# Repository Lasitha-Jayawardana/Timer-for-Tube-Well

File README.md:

# Timer-for-Tube-Well
Automated water filling system with dual motor including Tube well and upper tank.

# Tips
This include Arduino file and Eagle cad PCB project. And also Camout and CNC milling files are in here with.

First tank fill from the tube well using On and Off timer for tube well motor.
Second Tank fill from first tank by different motor.
Water level is measured by Sona Sensor in each tank. 
After full filled each tank, each motors are temporaly wait till water level goes down.

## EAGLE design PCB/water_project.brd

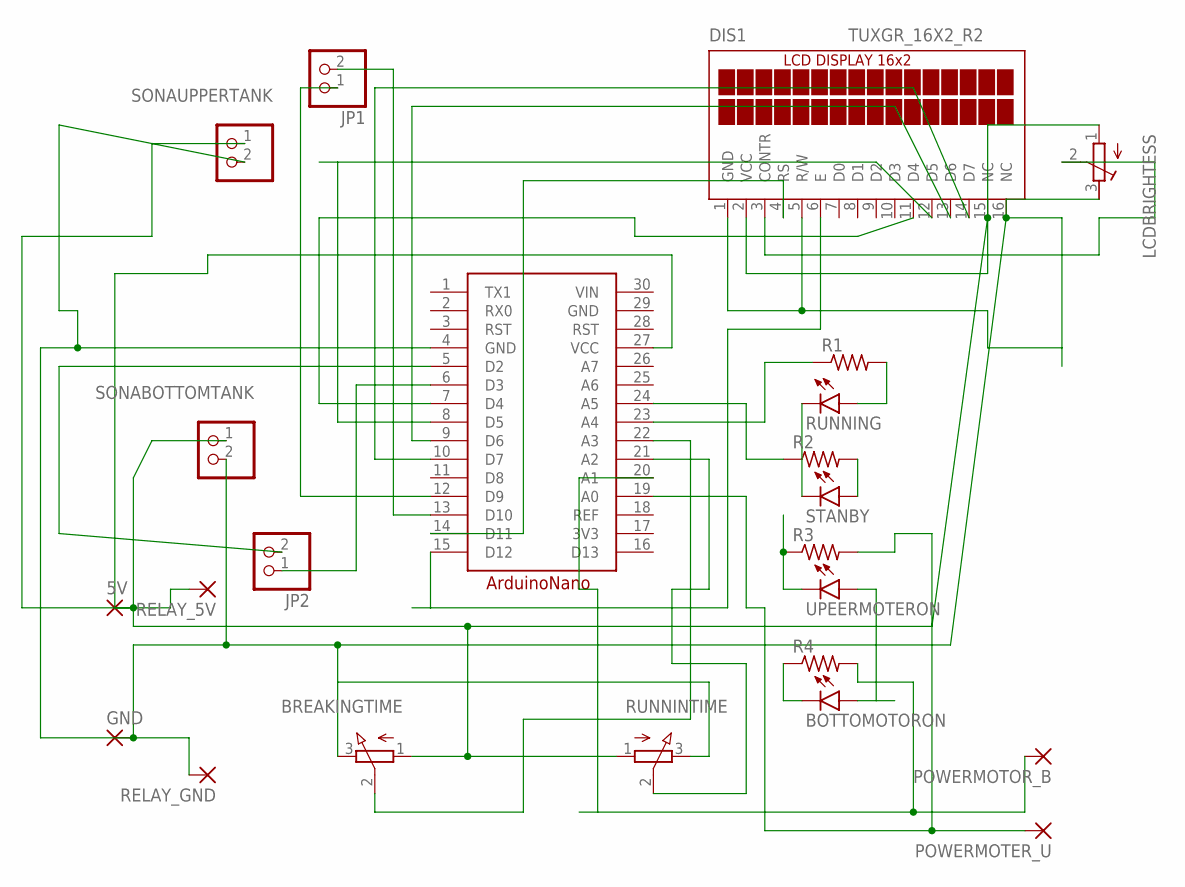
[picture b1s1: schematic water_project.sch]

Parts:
5V: 3,17/1,3
A1: ARDUINONANO
BOTTOMOTORON: LEDSFH480; SFH480
BREAKINGTIME: 3RP/1610N
DIS1: TUXGR_16X2_R2
GND: 3,17/1,3
JP1, JP2: PINHD-1X2; 1X02
LCDBRIGHTESS: R-TRIMM3339P; RTRIM3339P
POWERMOTER_U: 3,17/1,3
POWERMOTOR_B: 3,17/1,3
R1, R2, R3, R4: R-US_0207/7; 0207/7
RELAY_5V: 3,17/1,3
RELAY_GND: 3,17/1,3
RUNNING: LEDSFH480; SFH480
RUNNINTIME: 3RP/1610N
SONABOTTOMTANK: PINHD-1X2; 1X02
SONAUPPERTANK: PINHD-1X2; 1X02
STANBY: LEDSFH480; SFH480
UPEERMOTERON: LEDSFH480; SFH480

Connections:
3V3: A1.17 (3V3)
ECHO: A1.13 (D10), JP1.2
ECHO1: A1.5 (D2), JP2.2
GND: A1.4 (GND), A1.29 (GND), BREAKINGTIME.3 (E), DIS1.1 (GND), DIS1.5 (R/W), DIS1.16 (NC), GND.1, LCDBRIGHTESS.3 (E), RELAY_GND.1, RUNNINTIME.3 (E), SONABOTTOMTANK.2, SONAUPPERTANK.2
unnamed: R1.2, RUNNING.A
unnamed: R2.2, STANBY.A
unnamed: BOTTOMOTORON.K (C), R4.1
unnamed: DIS1.3 (CONTR), LCDBRIGHTESS.2 (S)
unnamed: A1.7 (D4), DIS1.11 (D4)
unnamed: A1.8 (D5), DIS1.12 (D5)
unnamed: A1.9 (D6), DIS1.13 (D6)
unnamed: A1.10 (D7), DIS1.14 (D7)
unnamed: RUNNING.K (C), STANBY.K (C)
unnamed: A1.14 (D11), DIS1.4 (RS)
unnamed: A1.15 (D12), DIS1.6 (E)
unnamed: A1.21 (A2), RUNNINTIME.2 (S)
unnamed: A1.22 (A3), BREAKINGTIME.2 (S)
unnamed: A1.19 (A0), POWERMOTER_U.1, R3.2
unnamed: A1.20 (A1), POWERMOTOR_B.1, R4.2
unnamed: A1.23 (A4), R1.1
unnamed: A1.24 (A5), R2.1
unnamed: R3.1, UPEERMOTERON.K (C)
REF: A1.18 (REF)
TRIG: A1.12 (D9), JP1.1
TRIG1: A1.6 (D3), JP2.1
VCC: 5V.1, A1.27 (VCC), BOTTOMOTORON.A, BREAKINGTIME.1 (A), DIS1.2 (VCC), DIS1.15 (NC), LCDBRIGHTESS.1 (A), RELAY_5V.1, RUNNINTIME.1 (A), SONABOTTOMTANK.1, SONAUPPERTANK.1, UPEERMOTERON.A
VIN: A1.30 (VIN)

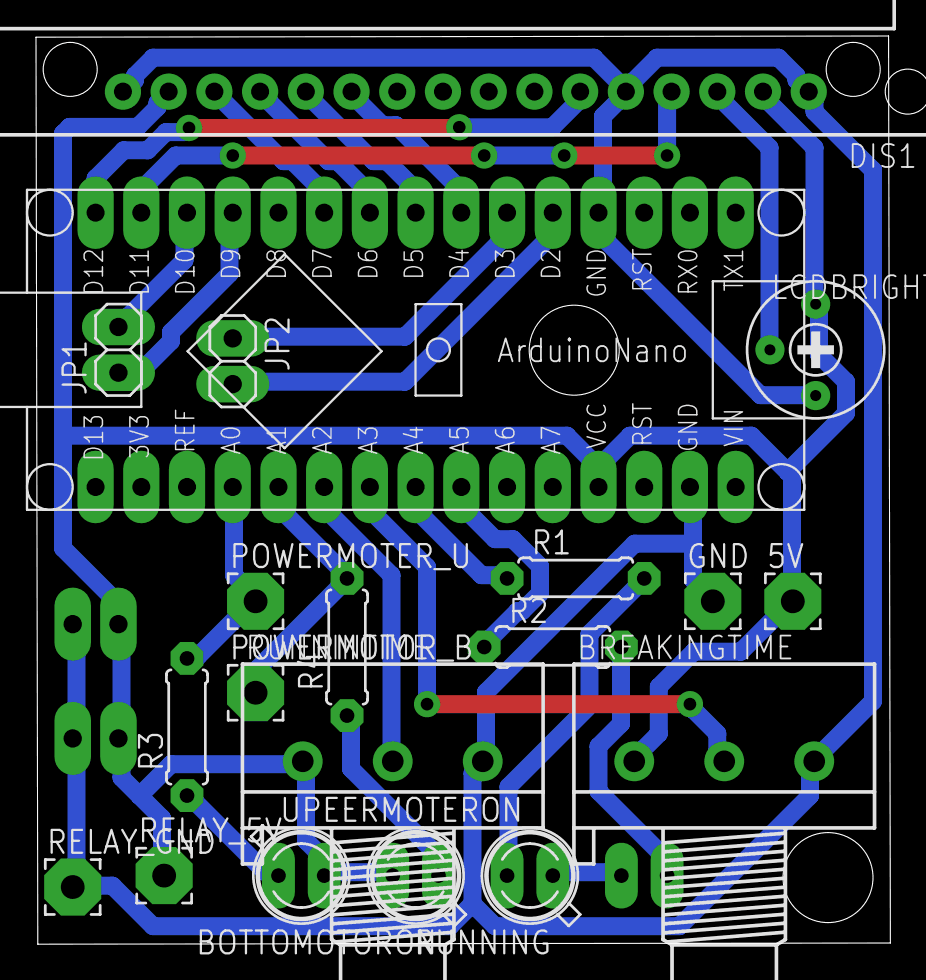
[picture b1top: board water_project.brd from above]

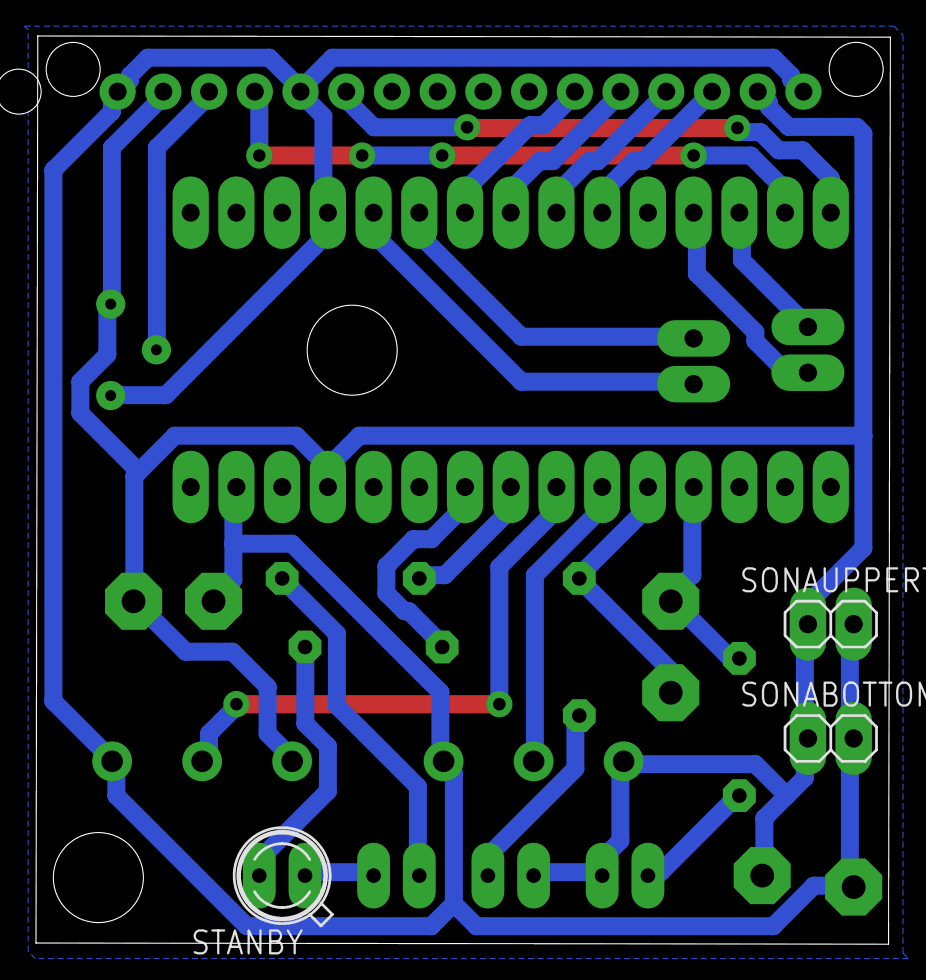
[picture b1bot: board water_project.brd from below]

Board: 2 copper layers, 47.5 x 50.5 mm, 23 parts (3 on the bottom side), 24 nets.

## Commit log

2020-11-18 Rename Dulsanka_Automated_Water_Filling_System.ino to Automated_Water_Filling_System(#Dulsanka).ino
2021-05-31 Emergency Mode added.
    Running time & Breaking time turn maximum before starting the device, Emergency Mode will be activated.
